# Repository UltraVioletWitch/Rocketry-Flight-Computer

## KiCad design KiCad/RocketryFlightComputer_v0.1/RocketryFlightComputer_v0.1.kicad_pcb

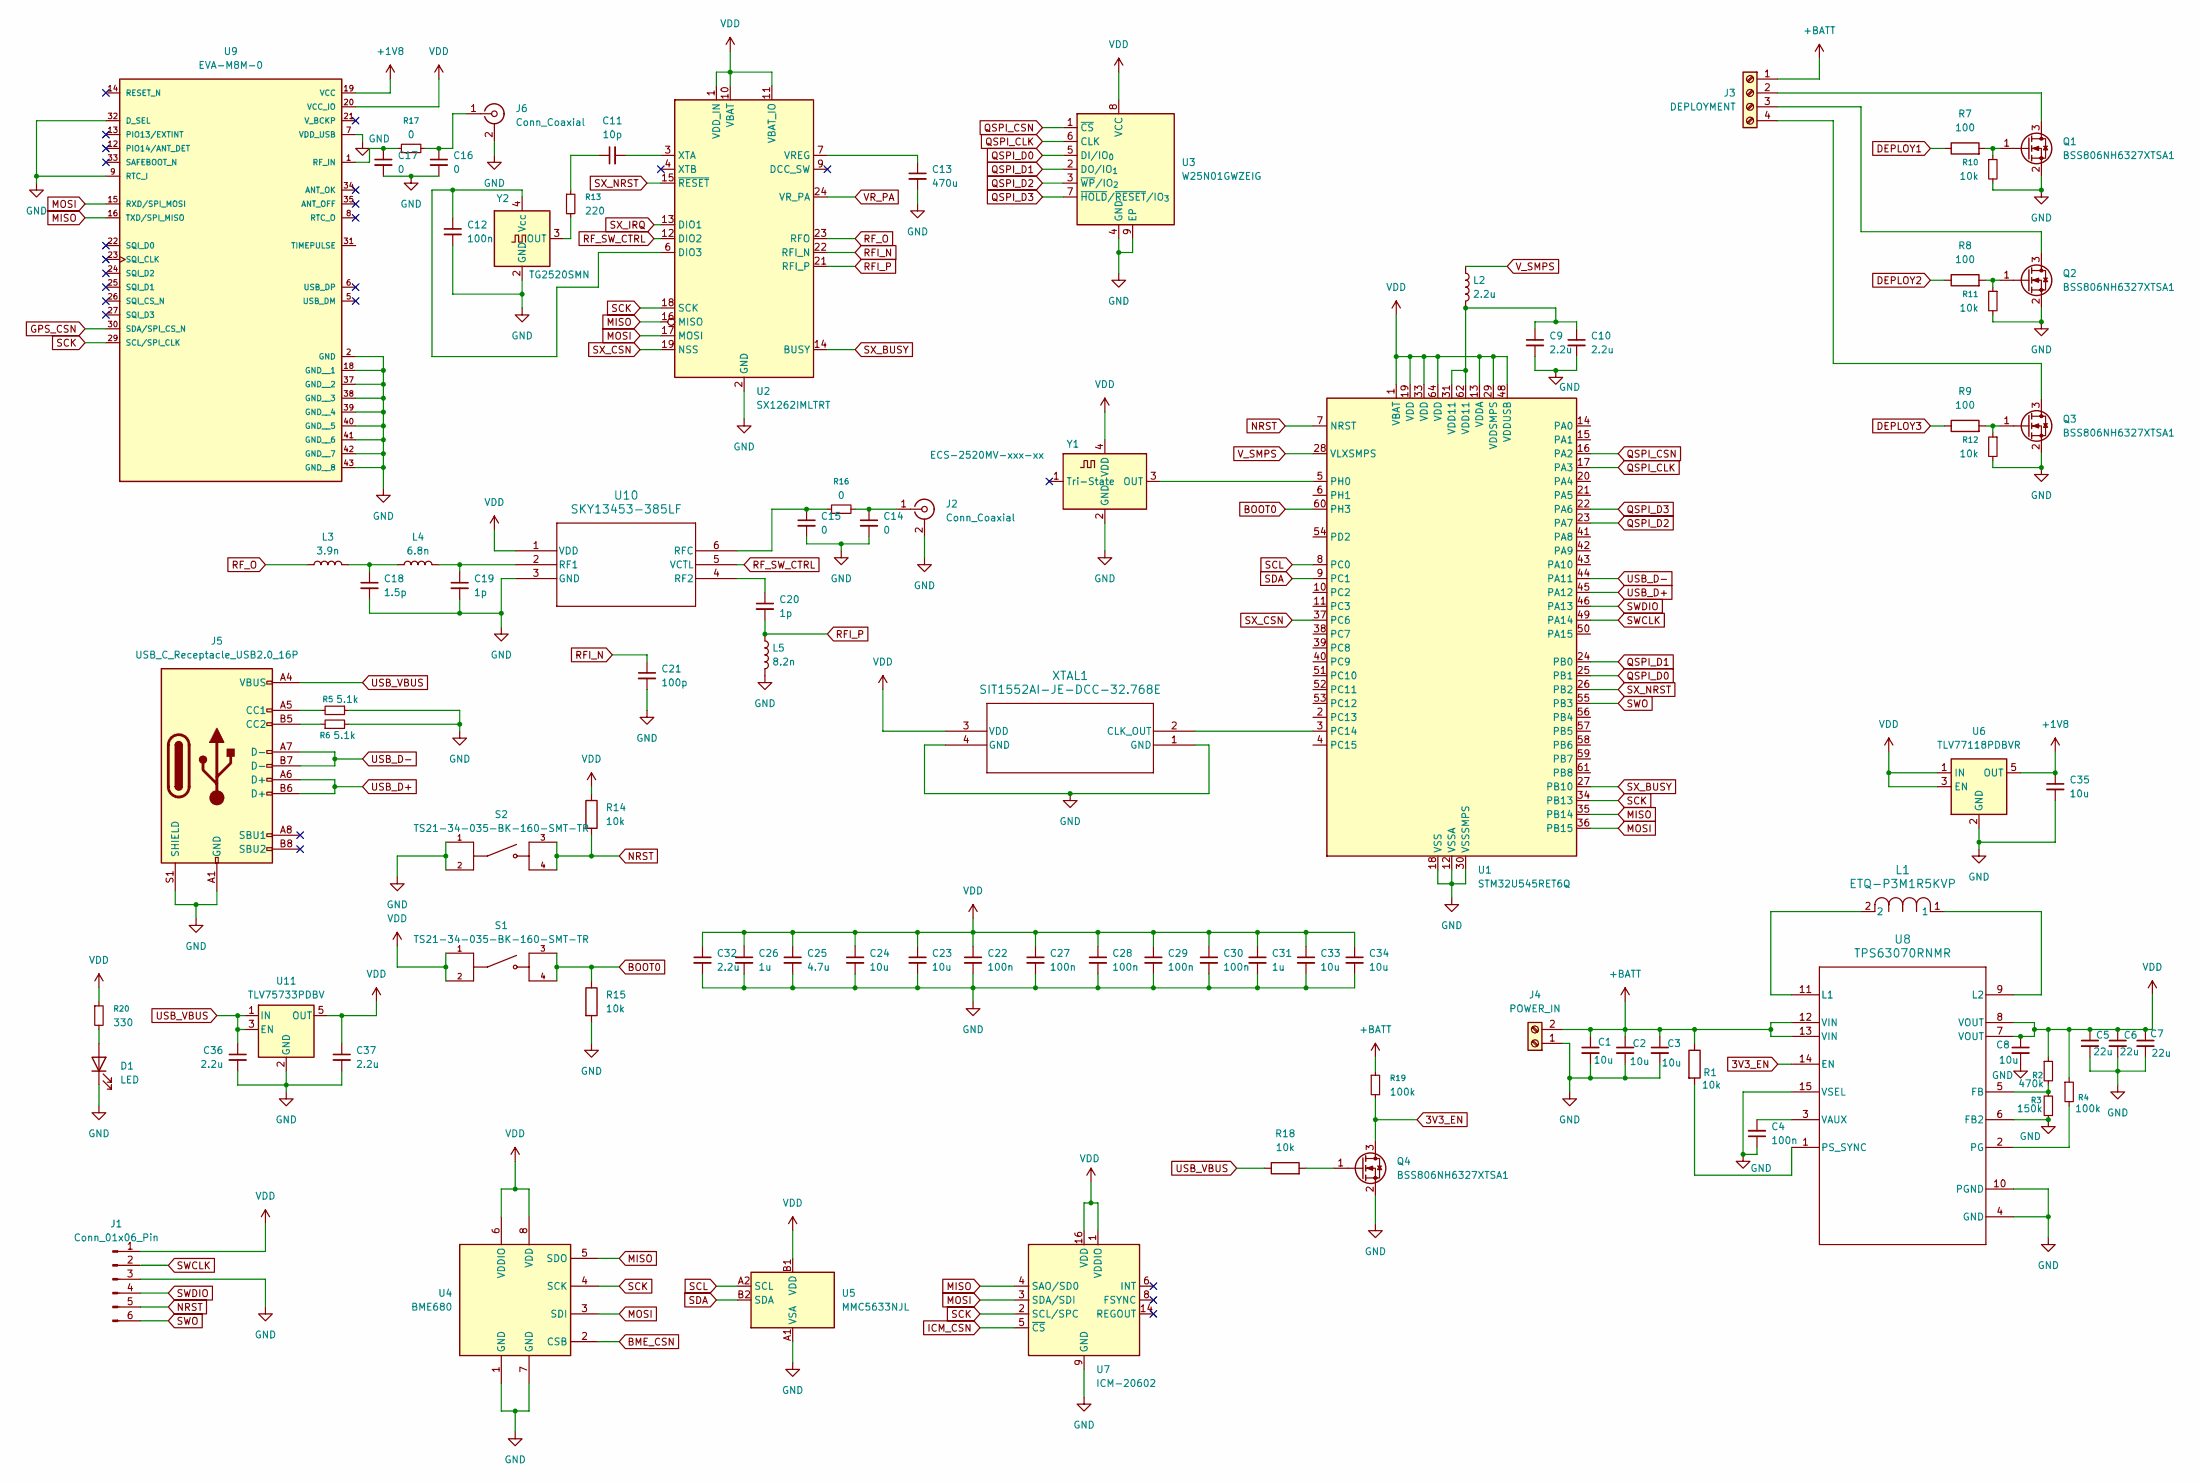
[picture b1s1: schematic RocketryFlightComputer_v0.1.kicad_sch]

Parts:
C1, C2: 10u; C_0805_2012Metric
C3, C8: 10u; C_0603_1608Metric
C4: 100n; C_0402_1005Metric
C5, C6, C7: 22u; C_0805_2012Metric
C9, C10: 2.2u; R_0402_1005Metric
C11: 10p; R_0402_1005Metric
C12: 100n; R_0402_1005Metric
C13: 470u; C_0402_1005Metric
C14, C15, C16, C17: 0; C_0402_1005Metric
C18: 1.5p; C_0201_0603Metric
C19, C20: 1p; C_0201_0603Metric
C21: 100p; C_0201_0603Metric
C22, C27, C28, C29, C30: 100n; C_0201_0603Metric
C23, C24, C33, C34, C35: 10u; C_0201_0603Metric
C25: 4.7u; C_0201_0603Metric
C26, C31: 1u; C_0201_0603Metric
C32, C36, C37: 2.2u; C_0201_0603Metric
D1: LED; LED_0402_1005Metric
J1: Conn_01x06_Pin; PinHeader_1x06_P1.00mm_Vertical_SMD_Pin1Left
J2, J6: Conn_Coaxial; U.FL_Hirose_U.FL-R-SMT-1_Vertical
J3: DEPLOYMENT; TerminalBlock_Phoenix_MPT-0,5-4-2.54_1x04_P2.54mm_Horizontal
J4: POWER_IN; TerminalBlock_Phoenix_MPT-0,5-2-2.54_1x02_P2.54mm_Horizontal
J5: USB_C_Receptacle_USB2.0_16P; USB_C_Receptacle_GCT_USB4105-xx-A_16P_TopMnt_Horizontal
L1: ETQ-P3M1R5KVP; L_Vishay_IHLP-1212
L2: 2.2u; C_0805_2012Metric
L3: 3.9n; L_0201_0603Metric
L4: 6.8n; L_0201_0603Metric
L5: 8.2n; L_0201_0603Metric
Q1, Q2, Q3, Q4: BSS806NH6327XTSA1; SOT-23
R1, R10, R11, R12: 10k; R_0402_1005Metric
R2: 470k; R_0402_1005Metric
R3: 150k; R_0402_1005Metric
R4: 100k; R_0402_1005Metric
R5, R6: 5.1k; R_0402_1005Metric
R7, R8, R9: 100; R_0402_1005Metric
R13: 220; R_0402_1005Metric
R14, R15: 10k; C_0402_1005Metric
R16, R17: 0; R_0402_1005Metric
R18: 10k; R_0201_0603Metric
R19: 100k; R_0201_0603Metric
R20: 330; R_0201_0603Metric
S1, S2: TS21-34-035-BK-160-SMT-TR; SW_TS21-34-035-BK-160-SMT-TR; PARTREV 1.01
U1: STM32U545RET6Q; LQFP-64_10x10mm_P0.5mm
U2: SX1262IMLTRT; QFN-24-1EP_4x4mm_P0.5mm_EP2.6x2.6mm
U3: W25N01GWZEIG; WSON-8-1EP_6x5mm_P1.27mm_EP3.4x4.3mm
U4: BME680; Bosch_LGA-8_3x3mm_P0.8mm_ClockwisePinNumbering
U5: MMC5633NJL; WLP-4_0.86x0.86mm_P0.4mm
U6: TLV77118PDBVR; SOT-23-5
U7: ICM-20602; LGA-16_3x3mm_P0.5mm_LayoutBorder3x5y
U8: TPS63070RNMR; RNM0015A
U9: EVA-M8M-0; LGA43R65P9X9_700X700X116; PART_REV R02
U10: SKY13453-385LF; QFN_453-385LF_SKY
U11: TLV75733PDBV; SOT-23-5
XTAL1: SIT1552AI-JE-DCC-32.768E; BGA4_SiT1532_SIT
Y1: ECS-2520MV-xxx-xx; Crystal_SMD_SeikoEpson_FA128-4Pin_2.0x1.6mm
Y2: TG2520SMN; Oscillator_SMD_SeikoEpson_TG2520SMN-xxx-xxxxxx-4Pin_2.5x2.0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

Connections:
3V3_EN: Q4.3 (D), R19.2, U8.14 (EN)
+1V8: C35.1, U6.5 (OUT), U9.19 (VCC)
+BATT: C1.1, C2.1, C3.1, J3.1, J4.2, R1.1, R19.1, U8.12 (VIN), U8.13 (VIN)
BME_CSN: U4.2 (CSB)
BOOT0: R15.1, S1.3, S1.4, U1.60 (PH3)
DEPLOY1: R7.1
DEPLOY2: R8.1
DEPLOY3: R9.1
GND: C1.2, C2.2, C3.2, C4.1, C5.2, C6.2, C7.2, C8.2, C9.2, C10.2, C12.2, C13.2, C14.2, C15.2, C16.2, C17.2, C18.2, C19.2, C21.2, C22.2, C23.2, C24.2, C25.2, C26.2, C27.2, C28.2, C29.2, C30.2, C31.2, C32.2, C33.2, C34.2, C35.2, C36.2, C37.2, D1.1 (K), J1.3, J2.2 (Ext), J4.1, J5.A1 (GND), J5.A12 (GND), J5.B1 (GND), J5.B12 (GND), J5.S1 (SHIELD), J6.2 (Ext), L5.2, Q1.2 (S), Q2.2 (S), Q3.2 (S), Q4.2 (S), R3.1, R5.1, R6.2, R10.2, R11.2, R12.2, R15.2, S2.1, S2.2, U1.12 (VSSA), U1.18 (VSS), U1.30 (VSSSMPS), U1.32 (VSS), U1.47 (VSS), U1.63 (VSS), U2.2 (GND), U2.5 (GND), U2.8 (GND), U2.20 (GND), U2.25 (GND), U3.4 (GND), U3.9 (EP), U4.1 (GND), U4.7 (GND), U5.A1 (VSA), U6.2 (GND), U6.4 (GND), U7.9 (GND), U7.10 (GND), U7.11 (GND), U7.12 (GND), U7.13 (GND), U7.15 (GND), U8.4 (GND), U8.6 (FB2), U8.10 (PGND), U8.15 (VSEL), U9.2 (GND), U9.7 (VDD_USB), U9.9 (RTC_I), U9.18 (GND__1), U9.32 (D_SEL), U9.37 (GND__2), U9.38 (GND__3), U9.39 (GND__4), U9.40 (GND__5), U9.41 (GND__6), U9.42 (GND__7), U9.43 (GND__8), U10.3 (GND), U11.2 (GND), XTAL1.1 (GND), XTAL1.4 (GND), Y1.2 (GND), Y2.2 (GND)
GPS_CSN: U9.30 (SDA/SPI_CS_N)
ICM_CSN: U7.5 (~CS)
MISO: U1.35 (PB14), U2.16 (MISO), U4.5 (SDO), U7.4 (SAO/SD0), U9.16 (TXD/SPI_MISO)
MOSI: U1.36 (PB15), U2.17 (MOSI), U4.3 (SDI), U7.3 (SDA/SDI), U9.15 (RXD/SPI_MOSI)
NRST: J1.5, R14.2, S2.3, S2.4, U1.7 (NRST)
unnamed: C9.1, C10.1, L2.2, U1.31 (VDD11), U1.62 (VDD11)
unnamed: C11.1, R13.1
unnamed: C18.1, L3.2, L4.1
unnamed: D1.2 (A), R20.2
unnamed: C14.1, J2.1 (In), R16.2
unnamed: J3.2, Q1.3 (D)
unnamed: J3.3, Q2.3 (D)
unnamed: J3.4, Q3.3 (D)
unnamed: J5.A5 (CC1), R5.2
unnamed: J5.B5 (CC2), R6.1
unnamed: C16.1, J6.1 (In), R17.2
unnamed: Q1.1 (G), R7.2, R10.1
unnamed: Q2.1 (G), R8.2, R11.1
unnamed: Q3.1 (G), R9.2, R12.1
unnamed: Q4.1 (G), R18.2
unnamed: U1.3 (PC14), XTAL1.2 (CLK_OUT)
unnamed: U1.5 (PH0), Y1.3 (OUT)
unnamed: C12.1, U2.6 (DIO3), Y2.4 (Vcc)
unnamed: C13.1, U2.7 (VREG)
unnamed: C11.2, U2.3 (XTA)
unnamed: R2.2, R3.2, U8.5 (FB)
unnamed: L1.2, U8.11 (L1)
unnamed: L1.1, U8.9 (L2)
unnamed: R4.2, U8.2 (PG)
unnamed: R1.2, U8.1 (PS_SYNC)
unnamed: C4.2, U8.3 (VAUX)
unnamed: C17.1, R17.1, U9.1 (RF_IN)
unnamed: C19.1, L4.2, U10.2 (RF1)
unnamed: C20.1, U10.4 (RF2)
unnamed: C15.1, R16.1, U10.6 (RFC)
unnamed: R13.2, Y2.3 (OUT)
QSPI_CLK: U1.17 (PA3), U3.6 (CLK)
QSPI_CSN: U1.16 (PA2), U3.1 (~CS)
QSPI_D0: U1.25 (PB1), U3.5 (DI/IO_{0})
QSPI_D1: U1.24 (PB0), U3.2 (DO/IO_{1})
QSPI_D2: U1.23 (PA7), U3.3 (~WP/IO_{2})
QSPI_D3: U1.22 (PA6), U3.7 (~HOLD/~RESET/IO_{3})
RFI_N: C21.1, U2.22 (RFI_N)
RFI_P: C20.2, L5.1, U2.21 (RFI_P)
RF_O: L3.1, U2.23 (RFO)
RF_SW_CTRL: U2.12 (DIO2), U10.5 (VCTL)
SCK: U1.34 (PB13), U2.18 (SCK), U4.4 (SCK), U7.2 (SCL/SPC), U9.29 (SCL/SPI_CLK)
SCL: U1.8 (PC0), U5.A2 (SCL)
SDA: U1.9 (PC1), U5.B2 (SDA)
SWCLK: J1.2, U1.49 (PA14)
SWDIO: J1.4, U1.46 (PA13)
SWO: J1.6, U1.55 (PB3)
SX_BUSY: U1.27 (PB10), U2.14 (BUSY)
SX_CSN: U1.37 (PC6), U2.19 (NSS)
SX_IRQ: U2.13 (DIO1)
SX_NRST: U1.26 (PB2), U2.15 (~RESET)
USB_D+: J5.A6 (D+), J5.B6 (D+), U1.45 (PA12)
USB_D-: J5.A7 (D-), J5.B7 (D-), U1.44 (PA11)
USB_VBUS: C36.1, J5.A4 (VBUS), J5.A9 (VBUS), J5.B4 (VBUS), J5.B9 (VBUS), R18.1, U11.1 (IN), U11.3 (EN)
VDD: C5.1, C6.1, C7.1, C8.1, C22.1, C23.1, C24.1, C25.1, C26.1, C27.1, C28.1, C29.1, C30.1, C31.1, C32.1, C33.1, C34.1, C37.1, J1.1, R2.1, R4.1, R14.1, R20.1, S1.1, S1.2, U1.1 (VBAT), U1.13 (VDDA), U1.19 (VDD), U1.29 (VDDSMPS), U1.33 (VDD), U1.48 (VDDUSB), U1.64 (VDD), U2.1 (VDD_IN), U2.10 (VBAT), U2.11 (VBAT_IO), U3.8 (VCC), U4.6 (VDDIO), U4.8 (VDD), U5.B1 (VDD), U6.1 (IN), U6.3 (EN), U7.1 (VDDIO), U7.16 (VDD), U8.7 (VOUT), U8.8 (VOUT), U9.20 (VCC_IO), U10.1 (VDD), U11.5 (OUT), XTAL1.3 (VDD), Y1.4 (VDD)
VR_PA: U2.24 (VR_PA)
V_SMPS: L2.1, U1.28 (VLXSMPS)

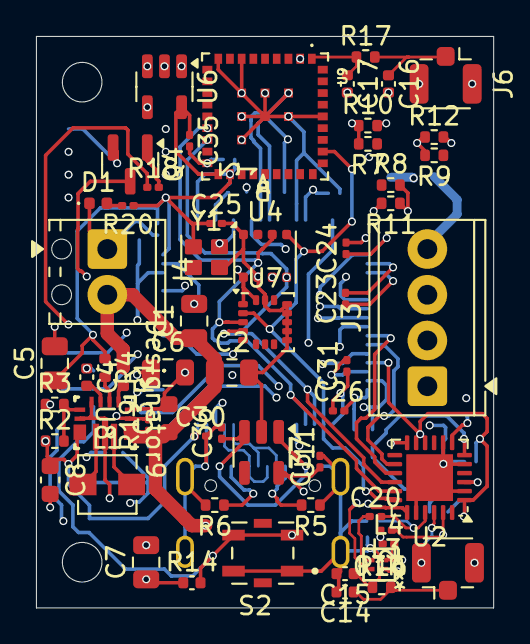
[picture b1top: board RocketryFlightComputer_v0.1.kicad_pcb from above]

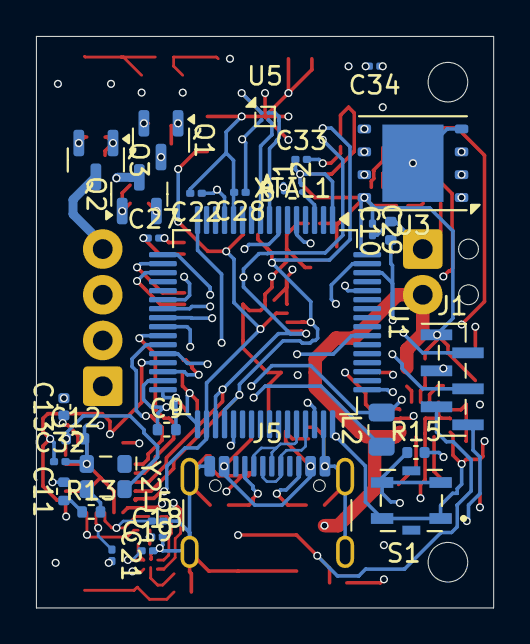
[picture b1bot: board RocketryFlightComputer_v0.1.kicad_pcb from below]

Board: 4 copper layers, 25.4 x 31.8 mm, 89 parts (30 on the bottom side), 63 nets.

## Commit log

2026-04-29 finished power supply
2026-05-11 Finished Board v0.1
